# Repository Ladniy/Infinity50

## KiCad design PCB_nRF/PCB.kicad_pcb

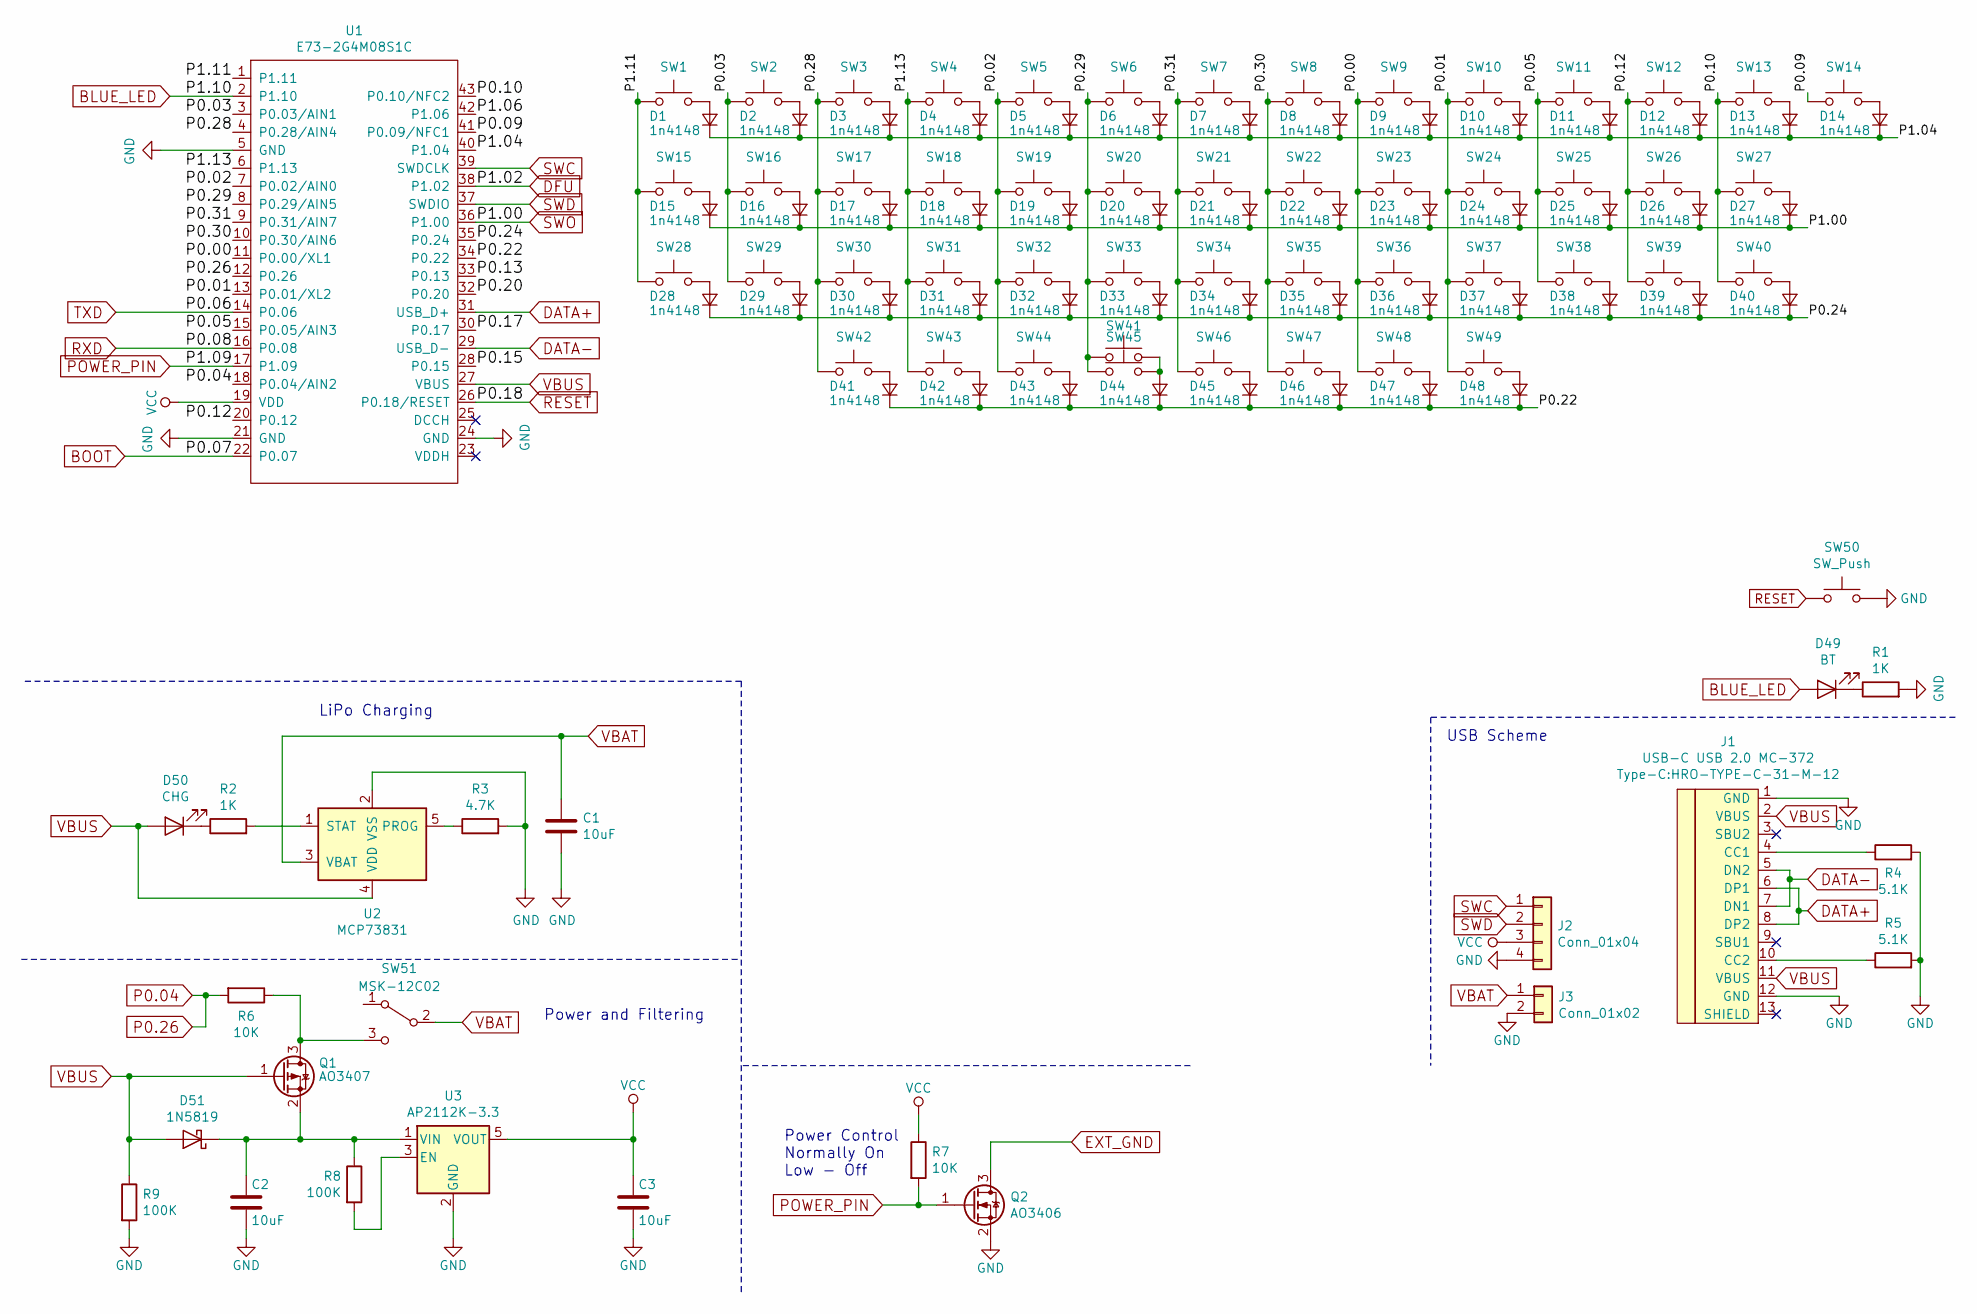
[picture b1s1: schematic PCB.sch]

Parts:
C1, C2, C3: 10uF; C_0603_1608Metric
D1, D2, D3, D4, D5, D6, D7, D8, D9, D10, D11, D12, D13, D14, D15, D16, D17, D18, D19, D20, D21, D22, D23, D24, D25, D26, D27, D28, D29, D30, D31, D32, D33, D34, D35, D36, D37, D38, D39, D40, D41, D42, D43, D44, D45, D46, D47, D48: 1n4148; Diode_SMD_SOD-123
D49: BT; LED_0603_1608Metric
D50: CHG; LED_0603_1608Metric
D51: 1N5819; D_SOD-123
J1: USB-C USB 2.0 MC-372; HRO-TYPE-C-31-M-12
J2: Conn_01x04; connector_swd
J3: Conn_01x02; connectro_bat
Q1: AO3407; SOT-23
Q2: AO3406; SOT-23
R1, R2: 1K; R_0603_1608Metric
R3: 4.7K; R_0603_1608Metric
R4, R5: 5.1K; R_0603_1608Metric
R6, R7: 10K; R_0603_1608Metric
R8, R9: 100K; R_0603_1608Metric
SW1, SW2, SW3, SW4, SW5, SW6, SW7, SW8, SW9, SW10, SW11, SW12, SW13, SW14, SW16, SW17, SW18, SW19, SW20, SW21, SW22, SW23, SW24, SW25, SW26, SW29, SW30, SW31, SW32, SW33, SW34, SW35, SW36, SW37, SW38, SW40, SW42, SW44, SW47, SW49: SW_Push; SW_MxHotswap_1u
SW15, SW39, SW43, SW48: SW_Push; SW_MxHotswap_1.25u
SW27, SW28: SW_Push; SW_MxHotswap_1.75u
SW41: SW_Push; SW_MxHotswap_7u
SW45: SW_Push; SW_MxHotswap_2.25u
SW46: SW_Push; SW_MxHotswap_2.75u
SW50: SW_Push; SW_SPST_TL3342
SW51: MSK-12C02; switch_MSK-12C02_smd
U1: E73-2G4M08S1C; E73-2G4M08S1C-52840
U2: MCP73831; SOT-23-5
U3: AP2112K-3.3; SOT-23-5

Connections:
/P0.00: SW9.1, SW23.1, SW36.1, SW48.1, U1.11 (P0.00/XL1)
/P0.01: SW10.1, SW24.1, SW37.1, SW49.1, U1.13 (P0.01/XL2)
/P0.02: SW5.1, SW19.1, SW32.1, SW44.1, U1.7 (P0.02/AIN0)
/P0.03: SW2.1, SW16.1, SW29.1, U1.3 (P0.03/AIN1)
/P0.05: SW11.1, SW25.1, SW38.1, U1.15 (P0.05/AIN3)
/P0.09: SW14.1, U1.41 (P0.09/NFC1)
/P0.10: SW13.1, SW27.1, SW40.1, U1.43 (P0.10/NFC2)
/P0.12: SW12.1, SW26.1, SW39.1, U1.20 (P0.12)
/P0.13: U1.33 (P0.13)
/P0.15: U1.28 (P0.15)
/P0.17: U1.30 (P0.17)
/P0.20: U1.32 (P0.20)
/P0.22: D41.1 (K), D42.1 (K), D43.1 (K), D44.1 (K), D45.1 (K), D46.1 (K), D47.1 (K), D48.1 (K), U1.34 (P0.22)
/P0.24: D28.1 (K), D29.1 (K), D30.1 (K), D31.1 (K), D32.1 (K), D33.1 (K), D34.1 (K), D35.1 (K), D36.1 (K), D37.1 (K), D38.1 (K), D39.1 (K), D40.1 (K), U1.35 (P0.24)
/P0.28: SW3.1, SW17.1, SW30.1, SW42.1, U1.4 (P0.28/AIN4)
/P0.29: SW6.1, SW20.1, SW33.1, SW41.1, SW45.1, U1.8 (P0.29/AIN5)
/P0.30: SW8.1, SW22.1, SW35.1, SW47.1, U1.10 (P0.30/AIN6)
/P0.31: SW7.1, SW21.1, SW34.1, SW46.1, U1.9 (P0.31/AIN7)
/P1.04: D1.1 (K), D2.1 (K), D3.1 (K), D4.1 (K), D5.1 (K), D6.1 (K), D7.1 (K), D8.1 (K), D9.1 (K), D10.1 (K), D11.1 (K), D12.1 (K), D13.1 (K), D14.1 (K), U1.40 (P1.04)
/P1.06: U1.42 (P1.06)
/P1.11: SW1.1, SW15.1, SW28.1, U1.1 (P1.11)
/P1.13: SW4.1, SW18.1, SW31.1, SW43.1, U1.6 (P1.13)
BLUE_LED: D49.2 (A), U1.2 (P1.10)
BOOT: U1.22 (P0.07)
DATA+: J1.6 (DP1), J1.8 (DP2), U1.31 (USB_D+)
DATA-: J1.5 (DN2), J1.7 (DN1), U1.29 (USB_D-)
DFU: U1.38 (P1.02)
EXT_GND: Q2.3 (D)
GND: C1.2, C2.2, C3.2, J1.1 (GND), J1.12 (GND), J2.4, J3.2, Q2.2 (S), R1.2, R3.2, R4.2, R5.2, R9.2, SW50.2, U1.5 (GND), U1.21 (GND), U1.24 (GND), U2.2 (VSS), U3.2 (GND)
unnamed: C2.1, D51.1 (K), Q1.2 (S), R8.1, U3.1 (VIN)
unnamed: D1.2 (A), SW1.2
unnamed: D2.2 (A), SW2.2
unnamed: D3.2 (A), SW3.2
unnamed: D4.2 (A), SW4.2
unnamed: D5.2 (A), SW5.2
unnamed: D6.2 (A), SW6.2
unnamed: D7.2 (A), SW7.2
unnamed: D8.2 (A), SW8.2
unnamed: D9.2 (A), SW9.2
unnamed: D10.2 (A), SW10.2
unnamed: D11.2 (A), SW11.2
unnamed: D12.2 (A), SW12.2
unnamed: D13.2 (A), SW13.2
unnamed: D14.2 (A), SW14.2
unnamed: D15.2 (A), SW15.2
unnamed: D16.2 (A), SW16.2
unnamed: D17.2 (A), SW17.2
unnamed: D18.2 (A), SW18.2
unnamed: D19.2 (A), SW19.2
unnamed: D20.2 (A), SW20.2
unnamed: D21.2 (A), SW21.2
unnamed: D22.2 (A), SW22.2
unnamed: D23.2 (A), SW23.2
unnamed: D24.2 (A), SW24.2
unnamed: D25.2 (A), SW25.2
unnamed: D26.2 (A), SW26.2
unnamed: D27.2 (A), SW27.2
unnamed: D28.2 (A), SW28.2
unnamed: D29.2 (A), SW29.2
unnamed: D30.2 (A), SW30.2
unnamed: D31.2 (A), SW31.2
unnamed: D32.2 (A), SW32.2
unnamed: D33.2 (A), SW33.2
unnamed: D34.2 (A), SW34.2
unnamed: D35.2 (A), SW35.2
unnamed: D36.2 (A), SW36.2
unnamed: D37.2 (A), SW37.2
unnamed: D38.2 (A), SW38.2
unnamed: D39.2 (A), SW39.2
unnamed: D40.2 (A), SW40.2
unnamed: D41.2 (A), SW42.2
unnamed: D42.2 (A), SW43.2
unnamed: D43.2 (A), SW44.2
unnamed: D44.2 (A), SW41.2, SW45.2
unnamed: D45.2 (A), SW46.2
unnamed: D46.2 (A), SW47.2
unnamed: D47.2 (A), SW48.2
unnamed: D48.2 (A), SW49.2
unnamed: D49.1 (K), R1.1
unnamed: D50.1 (K), R2.1
unnamed: J1.4 (CC1), R4.1
unnamed: J1.10 (CC2), R5.1
unnamed: Q1.3 (D), R6.1, SW51.3 (C)
unnamed: R2.2, U2.1 (STAT)
unnamed: R3.1, U2.5 (PROG)
unnamed: R8.2, U3.3 (EN)
P0.04: R6.2, U1.12 (P0.26), U1.18 (P0.04/AIN2)
POWER_PIN: Q2.1 (G), R7.2, U1.17 (P1.09)
RESET: SW50.1, U1.26 (P0.18/RESET)
RXD: U1.16 (P0.08)
SWC: J2.1, U1.39 (SWDCLK)
SWD: J2.2, U1.37 (SWDIO)
SWO: D15.1 (K), D16.1 (K), D17.1 (K), D18.1 (K), D19.1 (K), D20.1 (K), D21.1 (K), D22.1 (K), D23.1 (K), D24.1 (K), D25.1 (K), D26.1 (K), D27.1 (K), U1.36 (P1.00)
TXD: U1.14 (P0.06)
VBAT: C1.1, J3.1, SW51.2 (B), U2.3 (VBAT)
VBUS: D50.2 (A), D51.2 (A), J1.2 (VBUS), J1.11 (VBUS), Q1.1 (G), R9.1, U1.27 (VBUS), U2.4 (VDD)
VCC: C3.1, J2.3, R7.1, U1.19 (VDD), U3.5 (VOUT)

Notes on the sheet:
Power and Filtering
LiPo Charging
Power Control Normally On Low - Off
USB Scheme

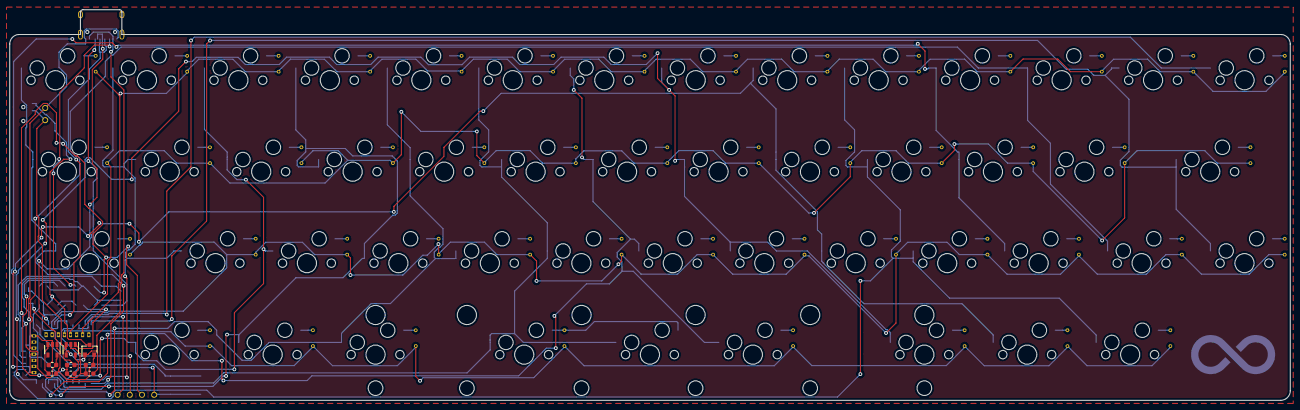
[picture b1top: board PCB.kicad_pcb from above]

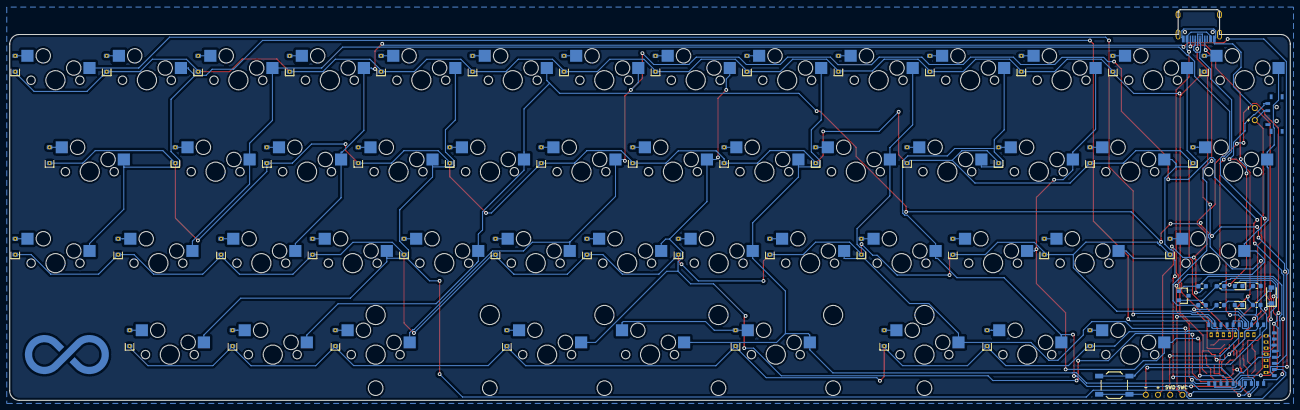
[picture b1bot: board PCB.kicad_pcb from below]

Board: 2 copper layers, 266.7 x 81.4 mm, 123 parts (16 on the bottom side), 87 nets.

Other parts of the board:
G1: LOGO; InfinityLogo

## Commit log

2020-01-06 Initial release
2020-01-22 Remove old case files
2020-01-22 Little update
2020-04-22 Clear .sch file
2020-04-22 Append nRFMicro schematic
2020-04-22 Complete matrix
2020-04-22 Add reset button
2020-04-22 Sort scheme
2020-04-22 Clear all annotation
2020-04-22 Anotate components
2020-04-22 ERC check
2020-04-27 Start PCB work
2020-04-27 Place diode
2020-04-27 Add marks for diodes
2020-04-27 Place SMD components
2020-04-27 Remove useless silkscreen
2020-04-27 Edit footprints
2020-04-27 Add design footprints
2020-04-27 Update route file
2020-04-27 Move power ports
2020-04-27 Route tracks
2020-04-27 Fill all zones
2020-04-27 Create 3D model of PCB
2020-04-27 Unfill all zones
2020-04-27 Remove middle flex hole
2020-04-27 Move components for better routing
2020-04-27 Make new text
2020-04-27 Remove flex hole
2020-04-28 Little fix
2020-04-28 Remove case catalog
2020-04-29 Create source file for case
2020-04-29 Autosave file
2020-04-29 Unfill all zones, increase angle radius
2020-04-30 Add main case frame
2020-04-30 Fillet angles
2020-05-28 Rename PCB folder
2020-05-28 Remove source file
2020-05-28 Append schematic
2020-06-02 Edit pro micro symbol
2020-06-03 Create 1.5u footprint
2020-06-03 Create Pro Micro footprint
2020-06-03 Make B+ pin rectangular
2020-06-03 Create battery pin footprint
2020-06-05 Add USB-C into schematic
2020-06-05 Add ESD protection diode
2020-06-05 Add 4 pit connector for USB
2020-06-05 Some design fix
2020-06-06 Reduce distance between pins by 2mm
2020-06-06 Rename battery pin
2020-06-06 Create footprint for USB-C wire
2020-06-06 Assign PCB footprint to schematic symbols
2020-06-06 Generate NET list file
